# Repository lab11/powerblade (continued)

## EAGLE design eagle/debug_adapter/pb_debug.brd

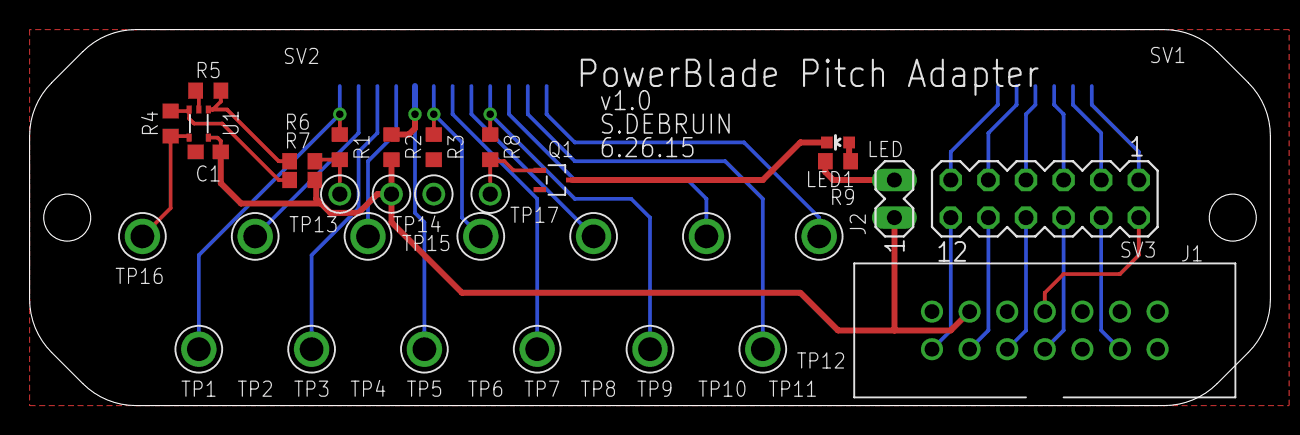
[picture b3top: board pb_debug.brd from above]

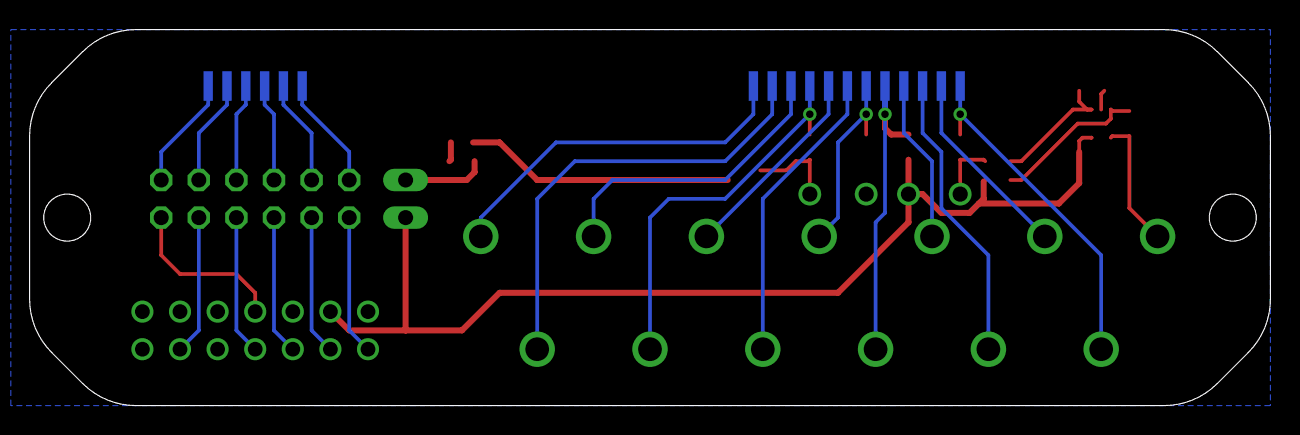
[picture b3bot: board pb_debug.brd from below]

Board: 2 copper layers, 83.8 x 25.4 mm, 35 parts (2 on the bottom side), 34 nets.

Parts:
C1: 0.1uF; C0603
J1: JTAG_14PIN_FULL; MA14-JTAG
J2: MA02-1STR; MA02-1
LED1: LED-0603
Q1: 2N7002; SC-70-3
R1, R2, R3: 0; R0603
R4, R5: 10k; R0603
R6, R7: 10; R0603
R8: R0603
R9: 240; R0603
SV1: MA06-1_1MM27_LONG
SV2: MA12-1_1MM27_LONG
SV3: MA06-2
TP1, TP2, TP3, TP4, TP5, TP6, TP7, TP8, TP9, TP10, TP11, TP12, TP16: TP_MULT
TP13, TP14, TP15, TP17: TP_STD; TP
U1: MAX9910; SC70-5

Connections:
!RST!: J1.!RST!, SV3.4
+3V3: C1.1, J1.VCC_TARGET, J2.1, R2.2, R7.1, TP14.P$1, U1.P5
GND: C1.2, J1.GND, Q1.P2, R3.2, R5.2, TP15.P$1, U1.P2
LED: Q1.P1, R8.2, TP17.P$1
unnamed: R1.1, SV2.P12, TP1.P$1
unnamed: SV2.P11, TP2.P$1
unnamed: SV2.P10, TP3.P$1
unnamed: SV2.P9, TP4.P$1
unnamed: R2.1, SV2.P8, TP5.P$1
unnamed: R3.1, SV2.P7, TP6.P$1
unnamed: SV1.P6, SV3.11
unnamed: SV2.P6, TP7.P$1
unnamed: SV2.P5, TP8.P$1
unnamed: R8.1, SV2.P4, TP9.P$1
unnamed: SV2.P3, TP10.P$1
unnamed: SV2.P2, TP11.P$1
unnamed: SV2.P1, TP12.P$1
unnamed: SV1.P5, SV3.9
unnamed: SV1.P4, SV3.7
unnamed: SV1.P3, SV3.5
unnamed: SV1.P2, SV3.3
unnamed: SV1.P1, SV3.1
unnamed: R5.1, R6.2, U1.P1
unnamed: R4.1, R7.2, U1.P3
unnamed: R4.2, TP16.P$1, U1.P4
unnamed: LED1.C, Q1.P3
unnamed: LED1.A, R9.1
unnamed: J2.2, R9.2
TCK: J1.TCK, SV3.6
TDI: J1.TDI, SV3.10
TDO: J1.TDO, SV3.12
TEST: J1.TEST, SV3.2
TMS: J1.TMS, SV3.8
V+: R1.2, R6.1, TP13.P$1

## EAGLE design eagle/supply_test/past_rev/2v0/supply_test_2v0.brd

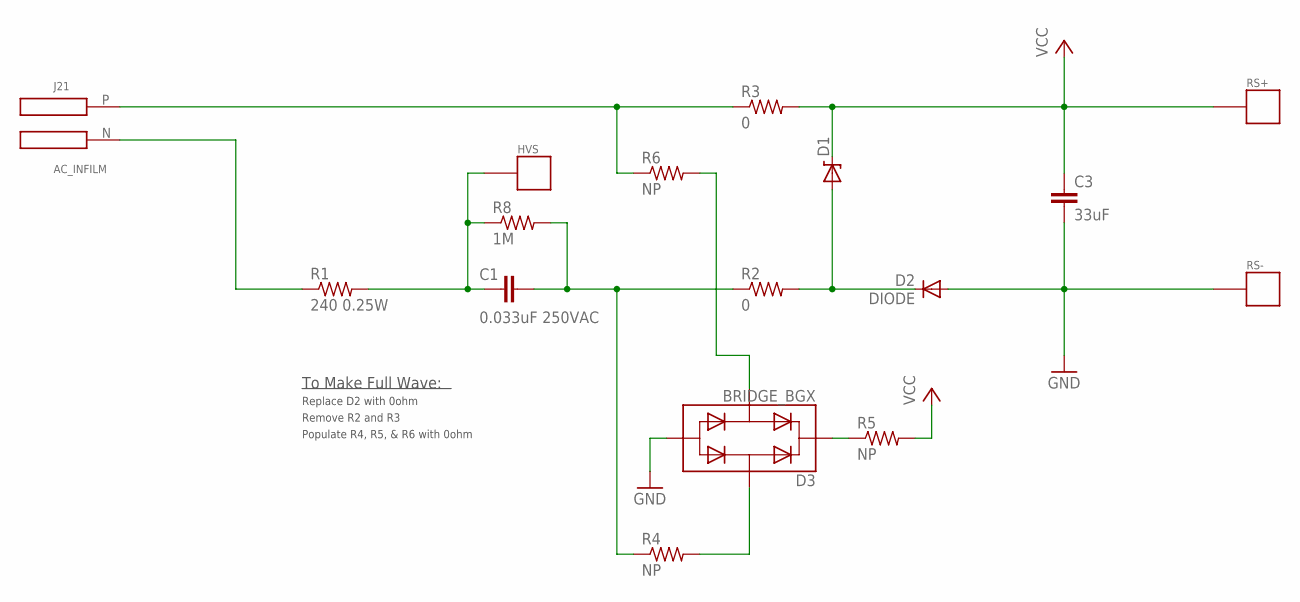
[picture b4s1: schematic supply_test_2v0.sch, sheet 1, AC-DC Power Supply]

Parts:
C1: 0.033uF 250VAC; C2220K; DIGIKEY 490-4238-1-ND
C3: 33uF; C0603; DIGIKEY 718-1672-1-ND
D1: ZENERBZT52; BZT52; DIGIKEY BZT52C10T-7DICT-ND
D2: DIODE; BAS521
D3: BRIDGE_BGX; TO-253-4
HVS: TP_STD; TP; DIGIKEY 5000K-ND
J21: AC_INFILM; AC3_FILM; DIGIKEY NP
R1: 240 0.25W; R0603; DIGIKEY RHM240DCT-ND
R2, R3: 0; R0603; DIGIKEY P0.0GCT-ND
R4, R5, R6: NP; R0603; DIGIKEY NP
R8: 1M; R0603; DIGIKEY MCT0603-1.00M-CFCT-ND
RS+: TP_STD; TP; DIGIKEY NP
RS-: TP_STD; TP; DIGIKEY NP

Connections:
GND: C3.2, D2.A, D3.P3, RS-.P$1; also elsewhere on the board
unnamed: C1.2, HVS.P$1, R1.2, R8.1
unnamed: J21.N, R1.1
unnamed: D1.A, D2.C, R2.2
unnamed: C1.1, R2.1, R4.1, R8.2
unnamed: D3.P4, R4.2
unnamed: J21.P, R3.1, R6.1
unnamed: D3.P1, R5.1
unnamed: D3.P2, R6.2
VCC: C3.1, D1.C, R3.2, R5.2, RS+.P$1; also elsewhere on the board

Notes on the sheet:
To Make Full Wave:
Replace D2 with 0ohm
Remove R2 and R3
Populate R4, R5, & R6 with 0ohm

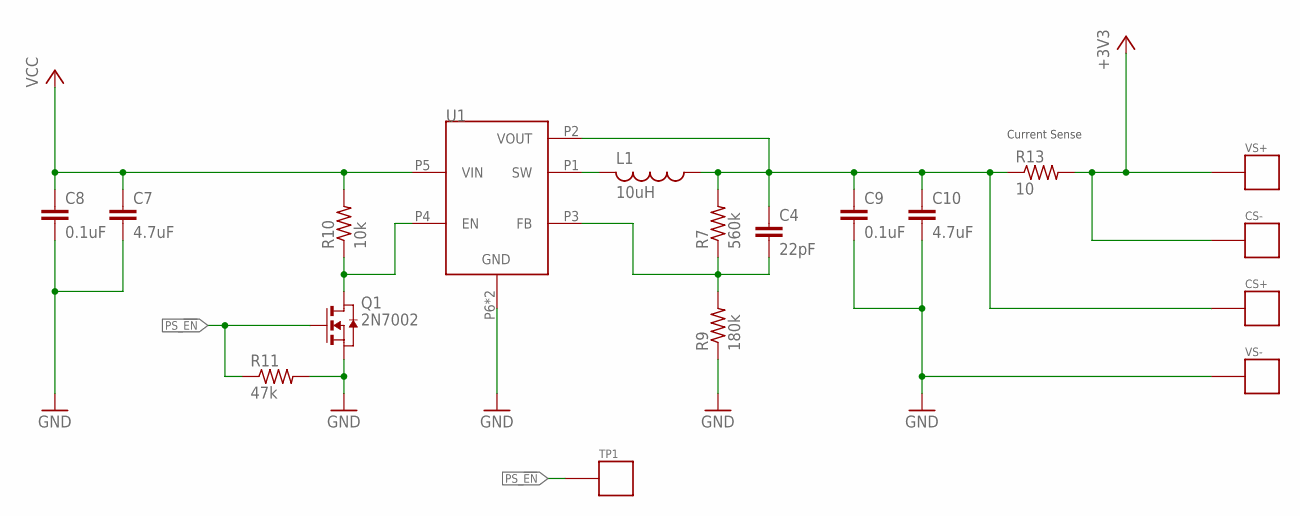
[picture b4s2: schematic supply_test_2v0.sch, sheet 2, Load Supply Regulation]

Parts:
C4: 22pF; C0603; DIGIKEY 399-1053-1-ND
C7: 4.7uF; C0402; DIGIKEY 587-2786-1-ND
C8, C9: 0.1uF; C0402; DIGIKEY 1276-1001-1-ND
C10: 4.7uF; C0603; DIGIKEY 587-2786-1-ND
CS+: TP_STD; TP; DIGIKEY NP
CS-: TP_STD; TP; DIGIKEY NP
L1: 10uH; L0805; DIGIKEY 490-4990-1-ND
Q1: 2N7002; SC-70-3
R7: 560k; R0603; DIGIKEY P560KHCT-ND
R9: 180k; R0603; DIGIKEY P180KHCT-ND
R10: 10k; R0402; DIGIKEY P10KJCT-ND
R11: 47k; R0603; DIGIKEY P47KGCT-ND
R13: 10; R0603; DIGIKEY CRT0603-BY-10R0ELFCT-ND
TP1: TP_STD; TP; DIGIKEY NP
U1: TPS62122; WDFN-6
VS+: TP_STD; TP; DIGIKEY NP
VS-: TP_STD; TP; DIGIKEY NP

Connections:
+3V3: CS-.P$1, R13.2, VS+.P$1; also elsewhere on the board
GND: C7.2, C8.2, C9.2, C10.2, Q1.P2 (S), R9.1, R11.2, U1.P6 (GND), U1.PAD (GND), VS-.P$1; also elsewhere on the board
unnamed: L1.2, U1.P1 (SW)
unnamed: C4.1, C9.1, C10.1, CS+.P$1, L1.1, R7.2, R13.1, U1.P2 (VOUT)
unnamed: C4.2, R7.1, R9.2, U1.P3 (FB)
unnamed: Q1.P3 (D), R10.1, U1.P4 (EN)
PS_!EN!: Q1.P1 (G), R11.1, TP1.P$1
VCC: C7.1, C8.1, R10.2, U1.P5 (VIN); also elsewhere on the board

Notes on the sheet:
Current Sense

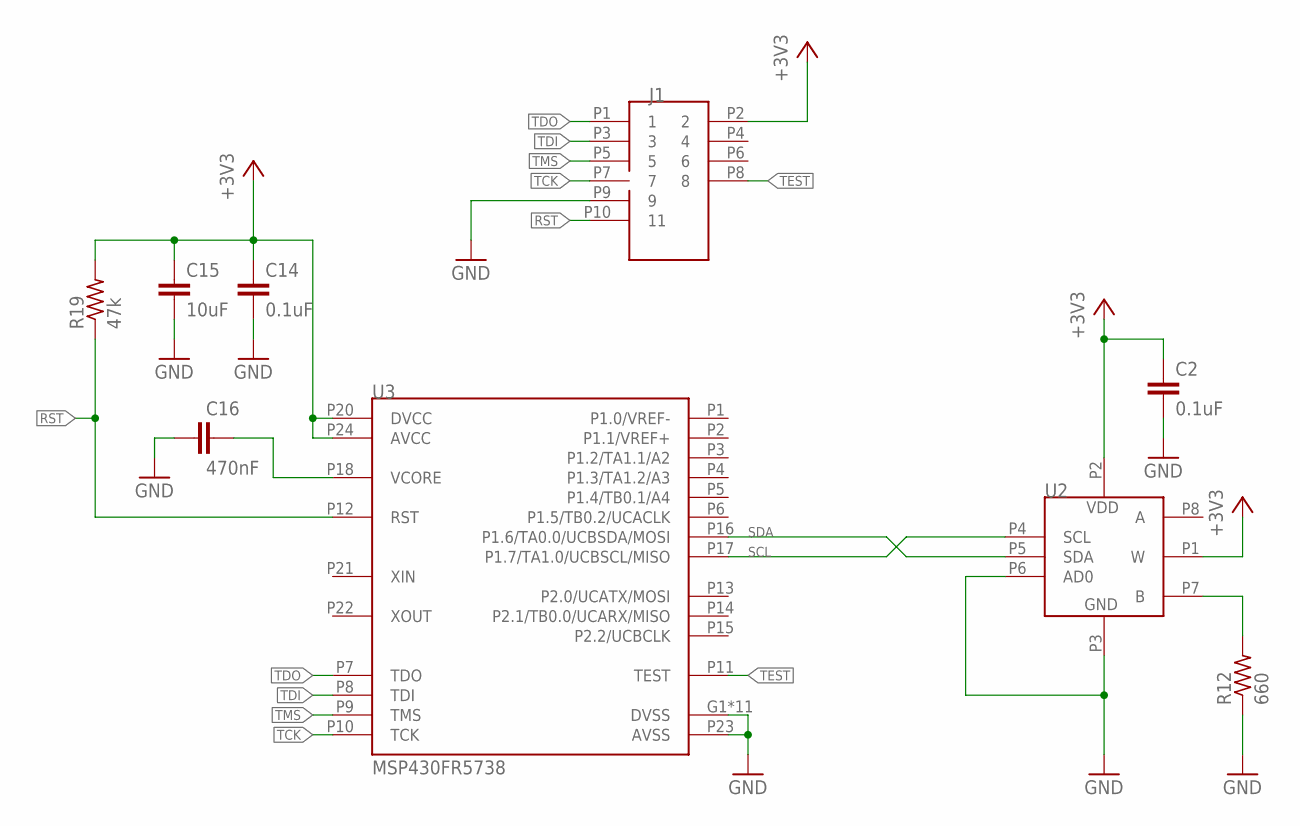
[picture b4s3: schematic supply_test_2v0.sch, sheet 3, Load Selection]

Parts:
C2, C14: 0.1uF; C0603; DIGIKEY 445-1316-1-ND
C15: 10uF; C0603; DIGIKEY 1276-1119-1-ND
C16: 470nF; C0603; DIGIKEY 445-5192-1-ND
J1: JTAG_14PIN_IDC-NL; TC2050-IDC-NL-430; DIGIKEY NP
R12: 660; R0603; DIGIKEY P665HCT-ND
R19: 47k; R0603; DIGIKEY P47KGCT-ND
U2: AD524; SOT-23-8
U3: MSP430FR5738; VQFN-24

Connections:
+3V3: C2.1, C14.1, C15.1, J1.P2 (2), R19.2, U2.P1 (W), U2.P2 (VDD), U3.P20 (DVCC), U3.P24 (AVCC); also elsewhere on the board
GND: C2.2, C14.2, C15.2, C16.1, J1.P9 (9), R12.1, U2.P3 (GND), U2.P6 (AD0), U3.G1 (DVSS), U3.G2 (DVSS), U3.G3 (DVSS), U3.G4 (DVSS), U3.G5 (DVSS), U3.G6 (DVSS), U3.G7 (DVSS), U3.G8 (DVSS), U3.G9 (DVSS), U3.P19 (DVSS), U3.P23 (AVSS), U3.PAD (DVSS); also elsewhere on the board
unnamed: R12.2, U2.P7 (B)
unnamed: C16.2, U3.P18 (VCORE)
RST: J1.P10 (11), R19.1, U3.P12 (RST)
SCL: U2.P4 (SCL), U3.P17 (P1.7/TA1.0/UCBSCL/MISO)
SDA: U2.P5 (SDA), U3.P16 (P1.6/TA0.0/UCBSDA/MOSI)
TCK: J1.P7 (7), U3.P10 (TCK)
TDI: J1.P3 (3), U3.P8 (TDI)
TDO: J1.P1 (1), U3.P7 (TDO)
TEST: J1.P8 (8), U3.P11 (TEST)
TMS: J1.P5 (5), U3.P9 (TMS)

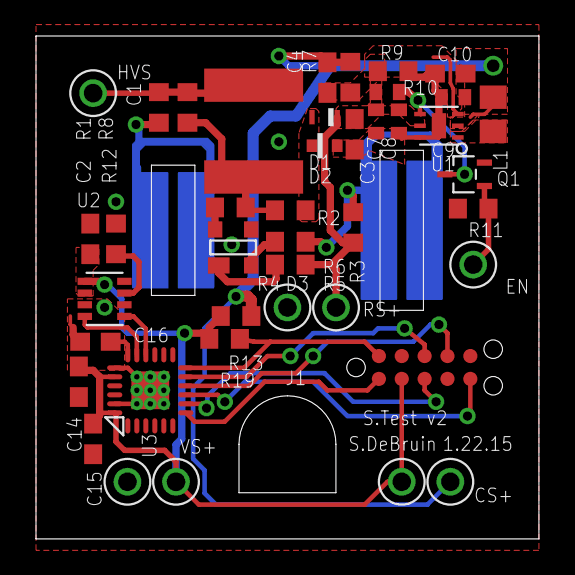
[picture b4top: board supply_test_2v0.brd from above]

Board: 2 copper layers, 27.9 x 27.9 mm, 43 parts (0 on the bottom side), 26 nets.

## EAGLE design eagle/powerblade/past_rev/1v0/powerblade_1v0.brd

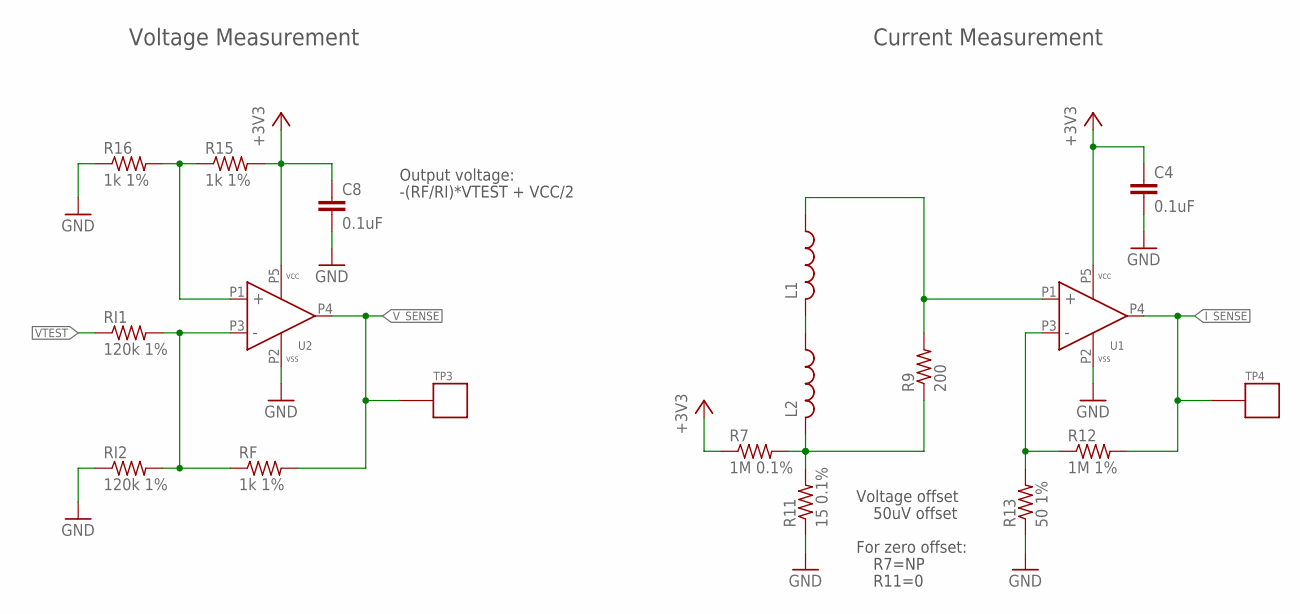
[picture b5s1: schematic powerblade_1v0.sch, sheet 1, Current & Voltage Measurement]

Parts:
C4, C8: 0.1uF; C0402; DIGIKEY 445-1265-1-ND
L1, L2: L-USL0805; L0805
R7: 1M 0.1%; R0603; DIGIKEY A102234CT-ND
R9: 200; R0603; DIGIKEY P200HCT-ND
R11: 15 0.1%; R0603; DIGIKEY A109933CT-ND
R12: 1M 1%; R0603; DIGIKEY A102234CT-ND
R13: 50 1%; R0603; DIGIKEY P49.9HCT-ND
R15, R16: 1k 1%; R0603; DIGIKEY P1.00KHCT-ND
RF: 1k 1%; R0603; DIGIKEY P1.00KHCT-ND
RI1, RI2: 120k 1%; R0603; DIGIKEY P120KHCT-ND
TP3, TP4: TP_STD; TP
U1, U2: MAX9910; SC70-5

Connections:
+3V3: C4.1, C8.1, R7.1, R15.2, U1.P5 (VCC), U2.P5 (VCC); also elsewhere on the board
GND: C4.2, C8.2, R11.1, R13.1, R16.1, RI2.1, U1.P2 (VSS), U2.P2 (VSS); also elsewhere on the board
I_SENSE: R12.2, TP4.P$1, U1.P4 (OUT); also elsewhere on the board
unnamed: R15.1, R16.2, U2.P1 (IN+)
unnamed: R12.1, R13.2, U1.P3 (IN-)
unnamed: RF.1, RI1.2, RI2.2, U2.P3 (IN-)
unnamed: L2.2, R7.2, R9.1, R11.2
unnamed: L1.1, R9.2, U1.P1 (IN+)
unnamed: L1.2, L2.1
VTEST: RI1.1; also elsewhere on the board
V_SENSE: RF.2, TP3.P$1, U2.P4 (OUT); also elsewhere on the board

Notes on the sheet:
Voltage offset
50uV offset
For zero offset:
R7=NP
R11=0
Current Measurement
Voltage Measurement
Output voltage:
-(RF/RI)*VTEST + VCC/2

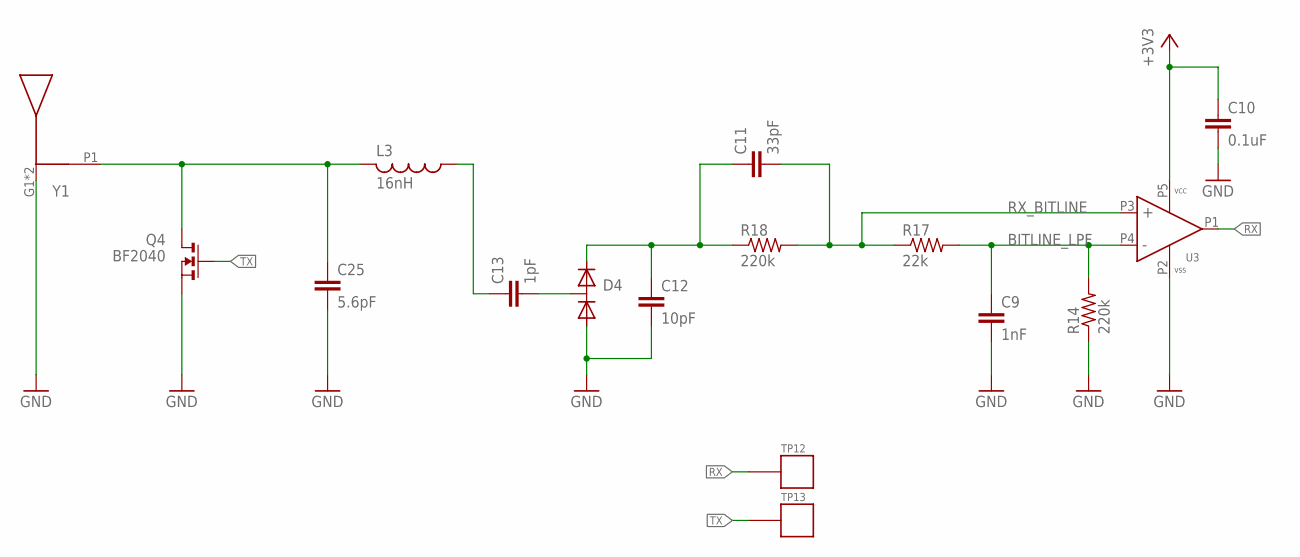
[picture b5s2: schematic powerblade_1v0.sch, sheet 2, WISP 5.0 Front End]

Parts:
C9: 1nF; C0603; DIGIKEY 490-6377-1-ND
C10: 0.1uF; C0603; DIGIKEY 445-1316-1-ND
C11: 33pF; C0603; DIGIKEY 399-7894-1-ND
C12: 10pF; C0603; DIGIKEY 1276-2151-1-ND
C13: 1pF; C0603; DIGIKEY 712-1323-1-ND
C25: 5.6pF; C0603; DIGIKEY 712-1360-1-ND
D4: HSMS-285C; SOT-323
L3: 16nH; L0603; DIGIKEY 732-1728-1-ND
Q4: BF2040; SOT-143
R14, R18: 220k; R0603; DIGIKEY P220KDBCT-ND
R17: 22k; R0603; DIGIKEY P22KDBCT-ND
TP12, TP13: TP_STD; TP
U3: NCS2200S; SC70-5
Y1: ANT-USP; DIGIKEY ANT-916-USP-ND

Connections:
+3V3: C10.1, U3.P5 (VCC); also elsewhere on the board
ANT: C25.1, L3.2, Q4.P2 (D), Y1.P1
BITLINE_LPF: C9.1, R14.2, R17.2, U3.P4 (IN-)
GND: C9.2, C10.2, C12.2, C25.2, D4.P1, Q4.P1 (S), R14.1, U3.P2 (VSS), Y1.G1 (G), Y1.G2 (G); also elsewhere on the board
unnamed: C13.1, L3.1
unnamed: C13.2, D4.P3
unnamed: C11.1, C12.1, D4.P2, R18.1
RX: TP12.P$1, U3.P1 (OUT); also elsewhere on the board
RX_BITLINE: C11.2, R17.1, R18.2, U3.P3 (IN+)
TX: Q4.P3 (G), Q4.P4 (G), TP13.P$1; also elsewhere on the board

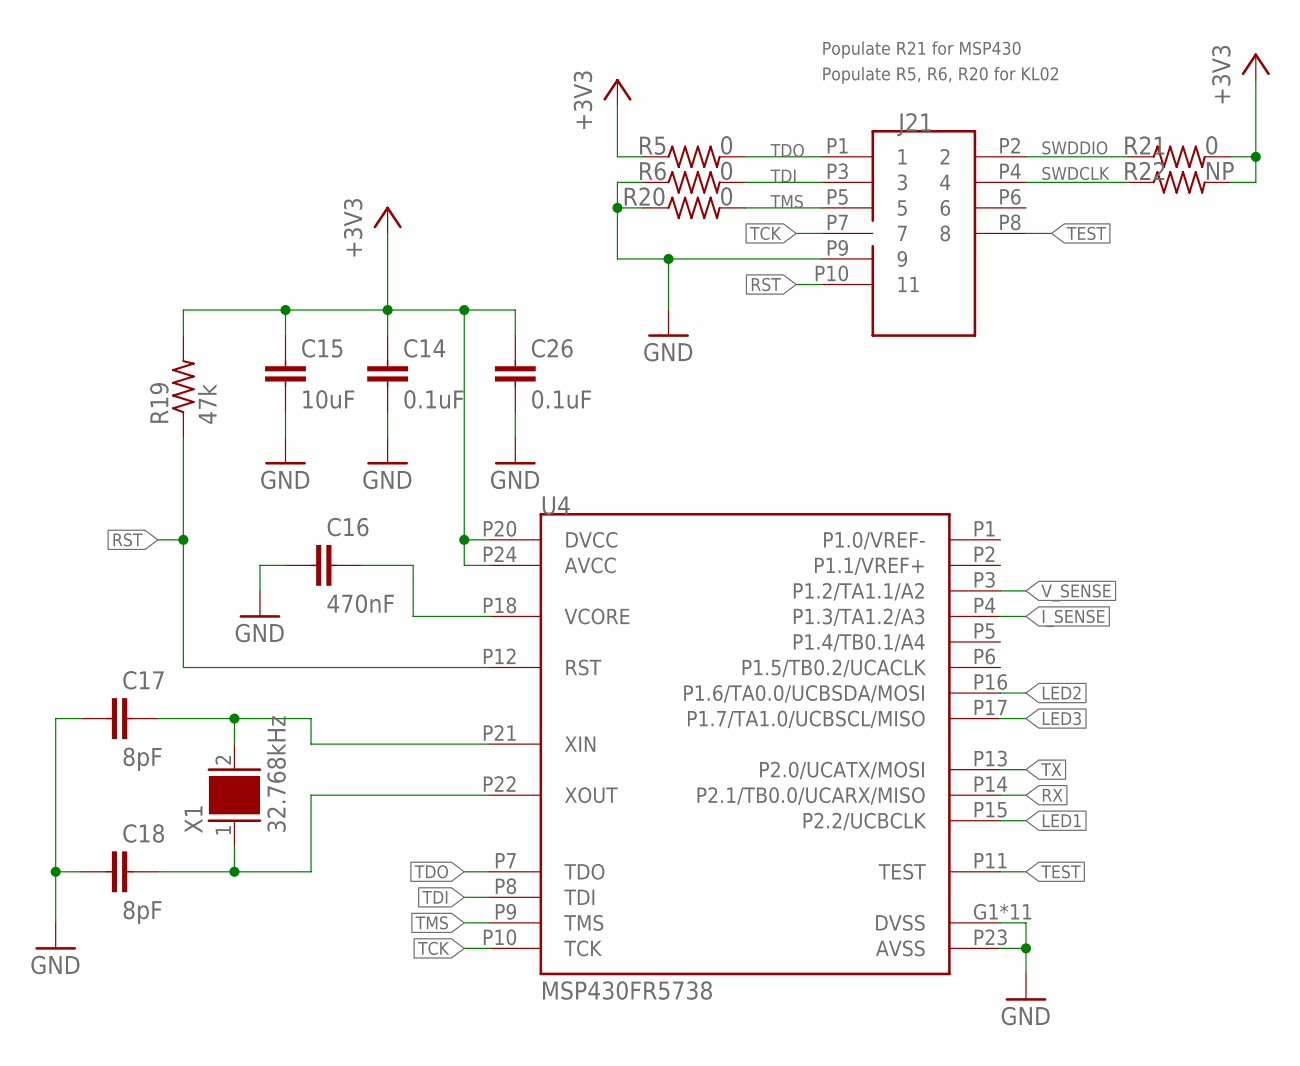
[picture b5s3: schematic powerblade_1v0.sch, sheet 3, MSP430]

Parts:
C14, C26: 0.1uF; C0603; DIGIKEY 445-1316-1-ND
C15: 10uF; C0603; DIGIKEY 1276-1119-1-ND
C16: 470nF; C0603; DIGIKEY 445-5192-1-ND
C17, C18: 8pF; C0603; DIGIKEY 1276-1817-1-ND
J21: JTAG_14PIN_IDC-NL; TC2050-IDC-NL-430; DIGIKEY NP
R5, R6, R20, R21: 0; R0603; DIGIKEY P0.0GCT-ND
R19: 47k; R0603; DIGIKEY P47KGCT-ND
R22: NP; R0603; DIGIKEY NP
U4: MSP430FR5738; VQFN-24
X1: 32.768kHz; 0805; DIGIKEY 535-12373-1-ND

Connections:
+3V3: C14.1, C15.1, C26.1, R5.1, R19.2, R21.2, R22.2, U4.P20 (DVCC), U4.P24 (AVCC); also elsewhere on the board
GND: C14.2, C15.2, C16.1, C17.1, C18.1, C26.2, J21.P9 (9), R6.1, R20.1, U4.G1 (DVSS), U4.G2 (DVSS), U4.G3 (DVSS), U4.G4 (DVSS), U4.G5 (DVSS), U4.G6 (DVSS), U4.G7 (DVSS), U4.G8 (DVSS), U4.G9 (DVSS), U4.P19 (DVSS), U4.P23 (AVSS), U4.PAD (DVSS); also elsewhere on the board
I_SENSE: U4.P4 (P1.3/TA1.2/A3); also elsewhere on the board
LED1: U4.P15 (P2.2/UCBCLK); also elsewhere on the board
LED2: U4.P16 (P1.6/TA0.0/UCBSDA/MOSI); also elsewhere on the board
LED3: U4.P17 (P1.7/TA1.0/UCBSCL/MISO); also elsewhere on the board
unnamed: C18.2, U4.P22 (XOUT), X1.1
unnamed: C16.2, U4.P18 (VCORE)
unnamed: C17.2, U4.P21 (XIN), X1.2
RST: J21.P10 (11), R19.1, U4.P12 (RST); also elsewhere on the board
RX: U4.P14 (P2.1/TB0.0/UCARX/MISO); also elsewhere on the board
SWDCLK: J21.P4 (4), R22.1; also elsewhere on the board
SWDDIO: J21.P2 (2), R21.1; also elsewhere on the board
TCK: J21.P7 (7), U4.P10 (TCK)
TDI: J21.P3 (3), R6.2, U4.P8 (TDI)
TDO: J21.P1 (1), R5.2, U4.P7 (TDO)
TEST: J21.P8 (8), U4.P11 (TEST)
TMS: J21.P5 (5), R20.2, U4.P9 (TMS)
TX: U4.P13 (P2.0/UCATX/MOSI); also elsewhere on the board
V_SENSE: U4.P3 (P1.2/TA1.1/A2); also elsewhere on the board

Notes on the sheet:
Populate R21 for MSP430
Populate R5, R6, R20 for KL02

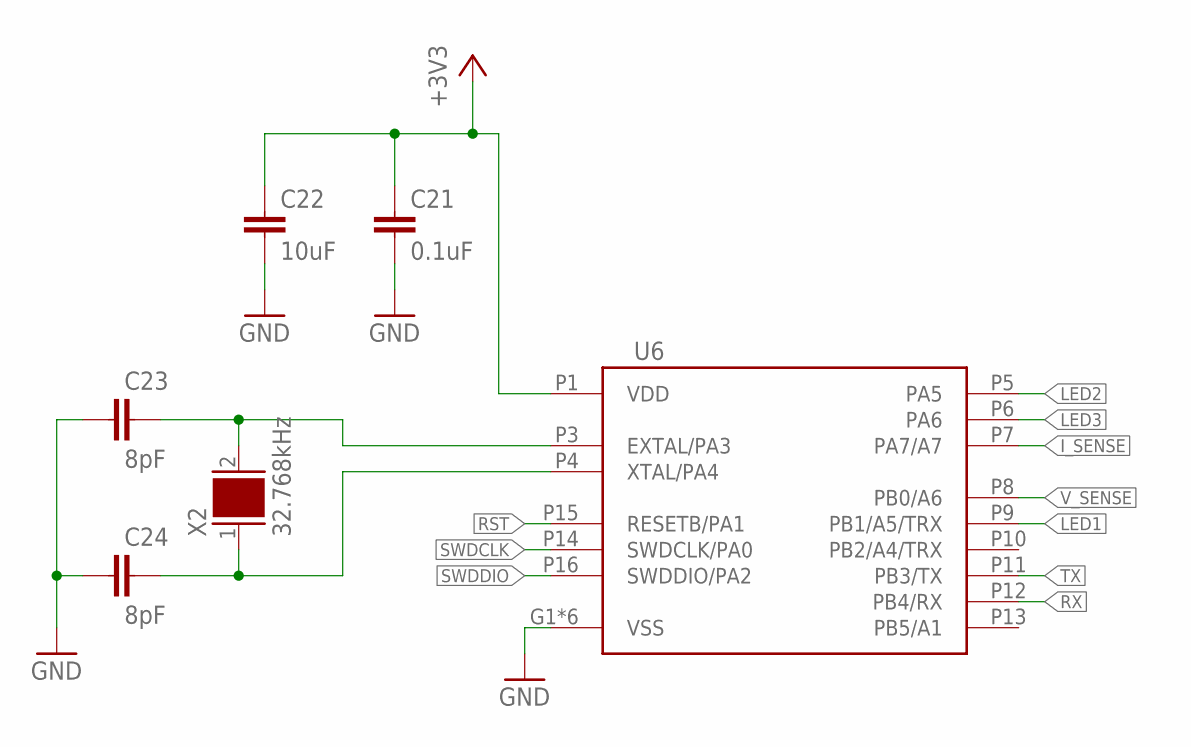
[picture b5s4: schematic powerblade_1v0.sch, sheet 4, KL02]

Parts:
C21: 0.1uF; C0603; DIGIKEY 445-1316-1-ND
C22: 10uF; C0603; DIGIKEY 1276-1119-1-ND
C23, C24: 8pF; C0603; DIGIKEY 1276-1817-1-ND
U6: KL02; WQFN-16
X2: 32.768kHz; 0805; DIGIKEY 535-12373-1-ND

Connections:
+3V3: C21.1, C22.1, U6.P1 (VDD); also elsewhere on the board
GND: C21.2, C22.2, C23.1, C24.1, U6.G1 (VSS), U6.G3 (VSS), U6.G7 (VSS), U6.G9 (VSS), U6.P2 (VSS), U6.PAD (VSS); also elsewhere on the board
I_SENSE: U6.P7 (PA7/A7); also elsewhere on the board
LED1: U6.P9 (PB1/A5/TRX); also elsewhere on the board
LED2: U6.P5 (PA5); also elsewhere on the board
LED3: U6.P6 (PA6); also elsewhere on the board
unnamed: C24.2, U6.P4 (XTAL/PA4), X2.1
unnamed: C23.2, U6.P3 (EXTAL/PA3), X2.2
RST: U6.P15 (RESETB/PA1); also elsewhere on the board
RX: U6.P12 (PB4/RX); also elsewhere on the board
SWDCLK: U6.P14 (SWDCLK/PA0); also elsewhere on the board
SWDDIO: U6.P16 (SWDDIO/PA2); also elsewhere on the board
TX: U6.P11 (PB3/TX); also elsewhere on the board
V_SENSE: U6.P8 (PB0/A6); also elsewhere on the board

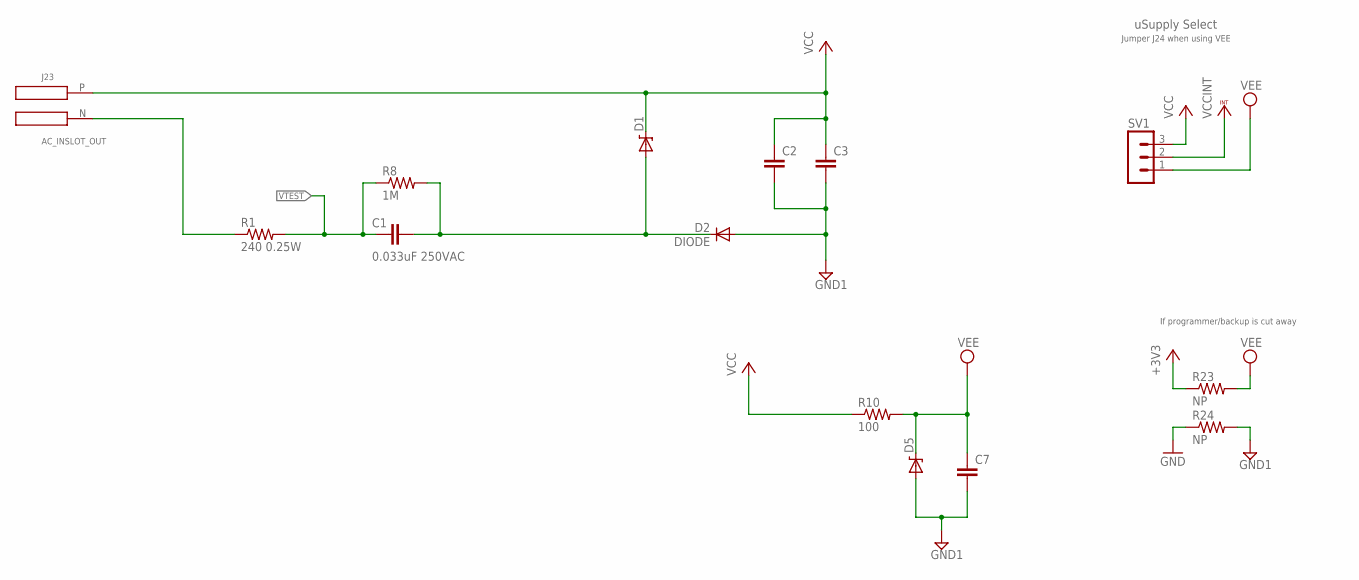
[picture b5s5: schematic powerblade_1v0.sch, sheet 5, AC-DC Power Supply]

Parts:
C1: 0.033uF 250VAC; C2220K; DIGIKEY 490-4238-1-ND
C2: C-EUC0805; C0805; DIGIKEY 445-8238-1-ND
C3: C-EUC0603; C0603; DIGIKEY 445-9077-1-ND
C7: C-EUC0603; C0603; DIGIKEY 1276-2383-1-ND
D1: ZENERBZT52; BZT52; DIGIKEY_2 BZT585B5V1T-7DICT-ND
D2: DIODE; BAS521
D5: ZENERBZT52; BZT52
J23: AC_INSLOT_OUT; AC_SLOT_OUT; DIGIKEY 3M11307-ND
R1: 240 0.25W; R0603; DIGIKEY RHM240DCT-ND
R8: 1M; R0603; DIGIKEY MCT0603-1.00M-CFCT-ND
R10: 100; R0603; DIGIKEY P100GCT-ND
R23, R24: NP; R0603; DIGIKEY NP
SV1: MA03-1STR; MA03-1; DIGIKEY 3M9448-ND

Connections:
+3V3: R23.1; also elsewhere on the board
GND: R24.1; also elsewhere on the board
GND1: C2.2, C3.2, C7.2, D2.A, D5.A, R24.2; also elsewhere on the board
unnamed: J23.N, R1.1
unnamed: C1.1, D1.A, D2.C, R8.2
VCC: C2.1, C3.1, D1.C, J23.P, R10.1, SV1.3
VCCINT: SV1.2; also elsewhere on the board
VEE: C7.1, D5.C, R10.2, R23.2, SV1.1
VTEST: C1.2, R1.2, R8.1; also elsewhere on the board

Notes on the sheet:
uSupply Select
Jumper J24 when using VEE
If programmer/backup is cut away

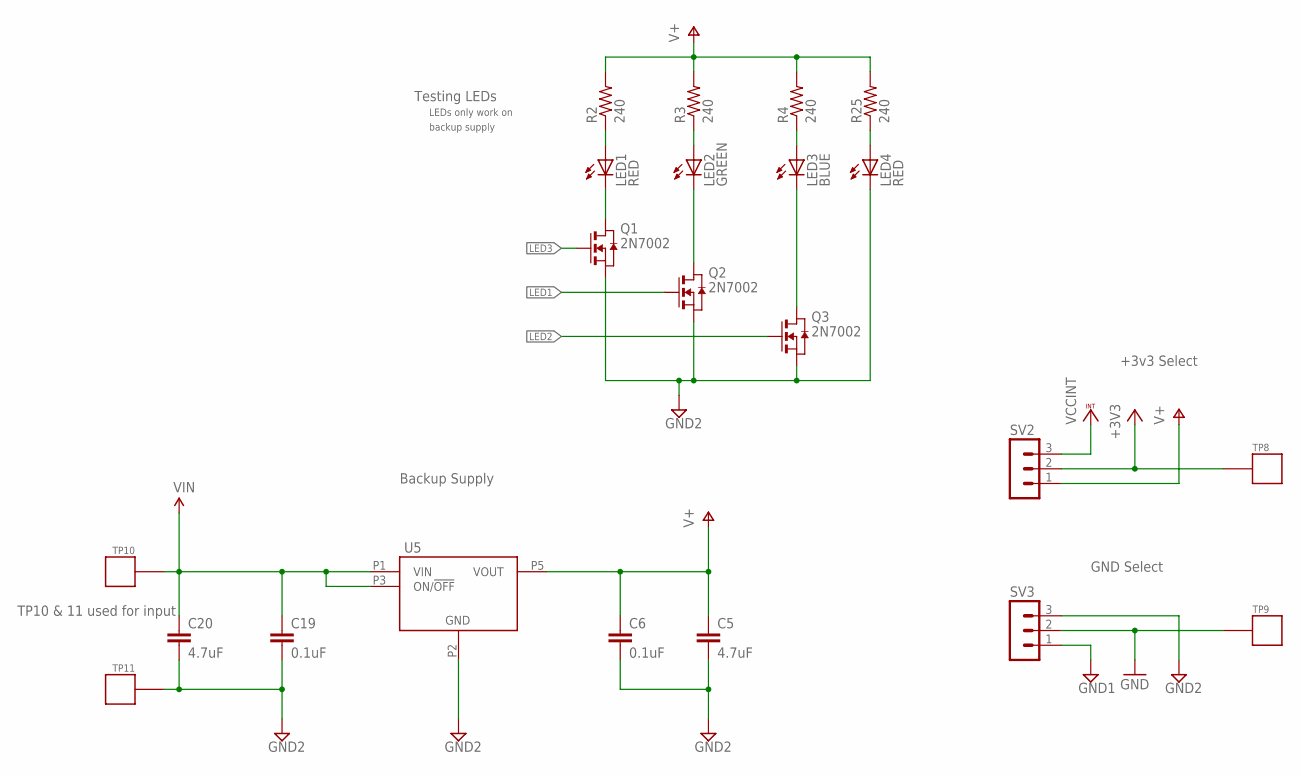
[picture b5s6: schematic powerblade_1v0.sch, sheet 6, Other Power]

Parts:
C5, C20: 4.7uF; C0603; DIGIKEY 490-3302-1-ND
C6, C19: 0.1uF; C0603; DIGIKEY 445-1316-1-ND
LED1, LED4: RED; LED-0603; DIGIKEY 1080-1400-1-ND
LED2: GREEN; LED-0603; DIGIKEY 1080-1402-1-ND
LED3: BLUE; LED-0603; DIGIKEY 1080-1401-1-ND
Q1, Q2, Q3: 2N7002; SC-70-3
R2, R3, R4, R25: 240; R0603; DIGIKEY P240GCT-ND
SV2, SV3: MA03-1STR; MA03-1; DIGIKEY 3M9448-ND
TP8, TP9, TP10, TP11: TP_STD; TP
U5: LP2980; SOT-23-5

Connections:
+3V3: SV2.2, TP8.P$1; also elsewhere on the board
GND: SV3.2, TP9.P$1; also elsewhere on the board
GND1: SV3.1; also elsewhere on the board
GND2: C5.2, C6.2, C19.2, C20.2, LED4.C, Q1.P2 (S), Q2.P2 (S), Q3.P2 (S), SV3.3, TP11.P$1, U5.P2 (GND)
LED1: Q2.P1 (G); also elsewhere on the board
LED2: Q3.P1 (G); also elsewhere on the board
LED3: Q1.P1 (G); also elsewhere on the board
unnamed: LED1.A, R2.1
unnamed: LED1.C, Q1.P3 (D)
unnamed: LED2.C, Q2.P3 (D)
unnamed: LED2.A, R3.1
unnamed: LED3.A, R4.1
unnamed: LED3.C, Q3.P3 (D)
unnamed: LED4.A, R25.1
V+: C5.1, C6.1, R2.2, R3.2, R4.2, R25.2, SV2.1, U5.P5 (VOUT)
VCCINT: SV2.3; also elsewhere on the board
VIN: C19.1, C20.1, TP10.P$1, U5.P1 (VIN), U5.P3 (ON/!OFF!)

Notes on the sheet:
+3v3 Select
GND Select
Backup Supply
Testing LEDs
LEDs only work on
backup supply
TP10 & 11 used for input

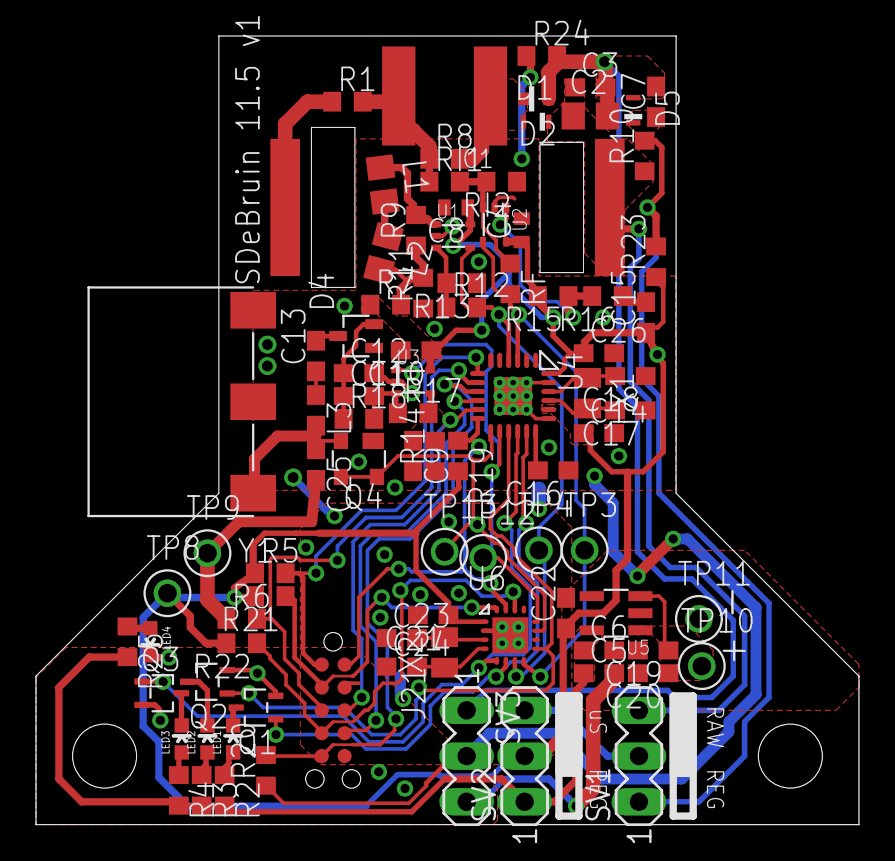
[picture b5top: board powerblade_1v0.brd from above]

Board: 2 copper layers, 45.7 x 43.8 mm, 91 parts (0 on the bottom side), 51 nets.
